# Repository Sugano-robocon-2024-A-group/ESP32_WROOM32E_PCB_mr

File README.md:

# ESP32_WROOM_32E_msd
## 作成・許諾 
Copyright (c) [2024] [益田隆太郎]. All rights reserved.
Sugano Robocon Aチーム (益田隆太郎、大谷卓輝、須崎一眞、藤上晃成)  
### * このソフトウェアパッケージは、3条項BSDライセンスの下、再配布及び使用が許可されます
### @ 2024 Sugano Robocon A team
連絡はX(@Masuda_moto)またはryutaro.masuda@akane.waseda.jpまで
## 外観

## 使用法
production→ESP32_WROOM_32E_msd.zipがガーバーファイルで、JLCPCBに送るとそのままPCBとして出してくれます。
## ピン配置
ESP32はESPマトリックス機能があるため、どのピンを使っても基本的に許されるが、PWMがはけるピンは決まっている。
[こちら](https://docs.sunfounder.com/projects/umsk/ja/latest/07_appendix/esp32_wroom_32e.html)を参照のこと
を参照のこと。
### 足回りピン配置
回路図の通りですが
RFはRightFront、LFはLeftFront、RBはRightBack、LBはLeftBackに対応しています。(例:RF_1とRF_2でモータドライバの正転逆転を制御、RF_PWMで角速度を制御)

GPIO22 RF_1  
GPIO23 RF_2  
GPIO16 RF_PWM  
GPIO18 LF_1  
GPIO19 LF_2  
GPIO21 LF_PWM  
GPIO32 RB_1  
GPIO33 RB_2  
GPIO04 RB_PWM  
GPIO25 LB_1  
GPIO14 LB_2  
GPIO13 LB_PWM  
足回りのモータドライバは[こちら](https://osoyoo.com/2022/02/25/osoyoo-model-y-4-channel-motor-driver/)の市販品を使用しました。

### CAN通信
いろんなサイトで26と27がRXとTXにアサインされていたので使用。うまく動きました。

GPIO26 CAN_RX  
GPIO27 CAN_TX  

### エンコーダピン配置
エンコーダで速度制御のフィードバックをかけたかったのですが、それだとピンが足りません。なのでマイコンを2個使って、CAN通信で情報をおくりあうことにしました。二つのマイコンの基板を共通化させたかったので、ピンを共有させました。
本番では速度のPID制御はあきらめてフィードフォワード制御に変えたので、このピンは使っていません。使いたかったら使うと良いと思います。
この場合、①RFとLFのモータを制御するマイコン②RBとLBのモータを制御するマイコン③上物を制御するマイコンの３つのマイコンでCAN通信をする必要があります。この時、CANバス内のノードが３つなので、終端抵抗を一つの基板だけOFFにする必要があります。SW1はそれ用のスイッチです。
また、ピンが共通になっているので、①のマイコンにおいて

GPIO22 RF_1  
GPIO23 RF_2  
GPIO16 RF_PWM  
GPIO18 LF_1  
GPIO19 LF_2  
GPIO21 LF_PWM  

をモータドライバに接続するときは、エンコーダに接続するピンは

GPIO32 RB_1  
GPIO33 RB_2  
GPIO25 LB_1  
GPIO14 LB_2  

であるという紛らわしさに注意する必要があります。②はその逆で、

GPIO32 RB_1  
GPIO33 RB_2  
GPIO04 RB_PWM  
GPIO25 LB_1  
GPIO14 LB_2  
GPIO13 LB_PWM  

をモータドライバに接続するので、エンコーダに接続するピンは

GPIO22 RF_1  
GPIO23 RF_2  
GPIO18 LF_1  
GPIO19 LF_2  

です。回路図の通りですね。
### 上物
投擲用のモータドライバは秋月で買える[TB67H450](https://akizukidenshi.com/catalog/g/g114753/)を使いました。
投擲のモータは速度フィードバックはかけず、フィードフォワードのみです。

GPIO16 RF_PWM 正転・逆転  
GPIO21 LF_PWM 正転・逆転  
GPIO04 RB_PWM PWM調整  

です。

GPIO13 LB_PWM  
GPIO05 Servo1  

を装填・仰角調整にアサインしました。
上物の電源電圧は2Sのリポバッテリー7.4Vを使用しました。XT30がコネクタです。

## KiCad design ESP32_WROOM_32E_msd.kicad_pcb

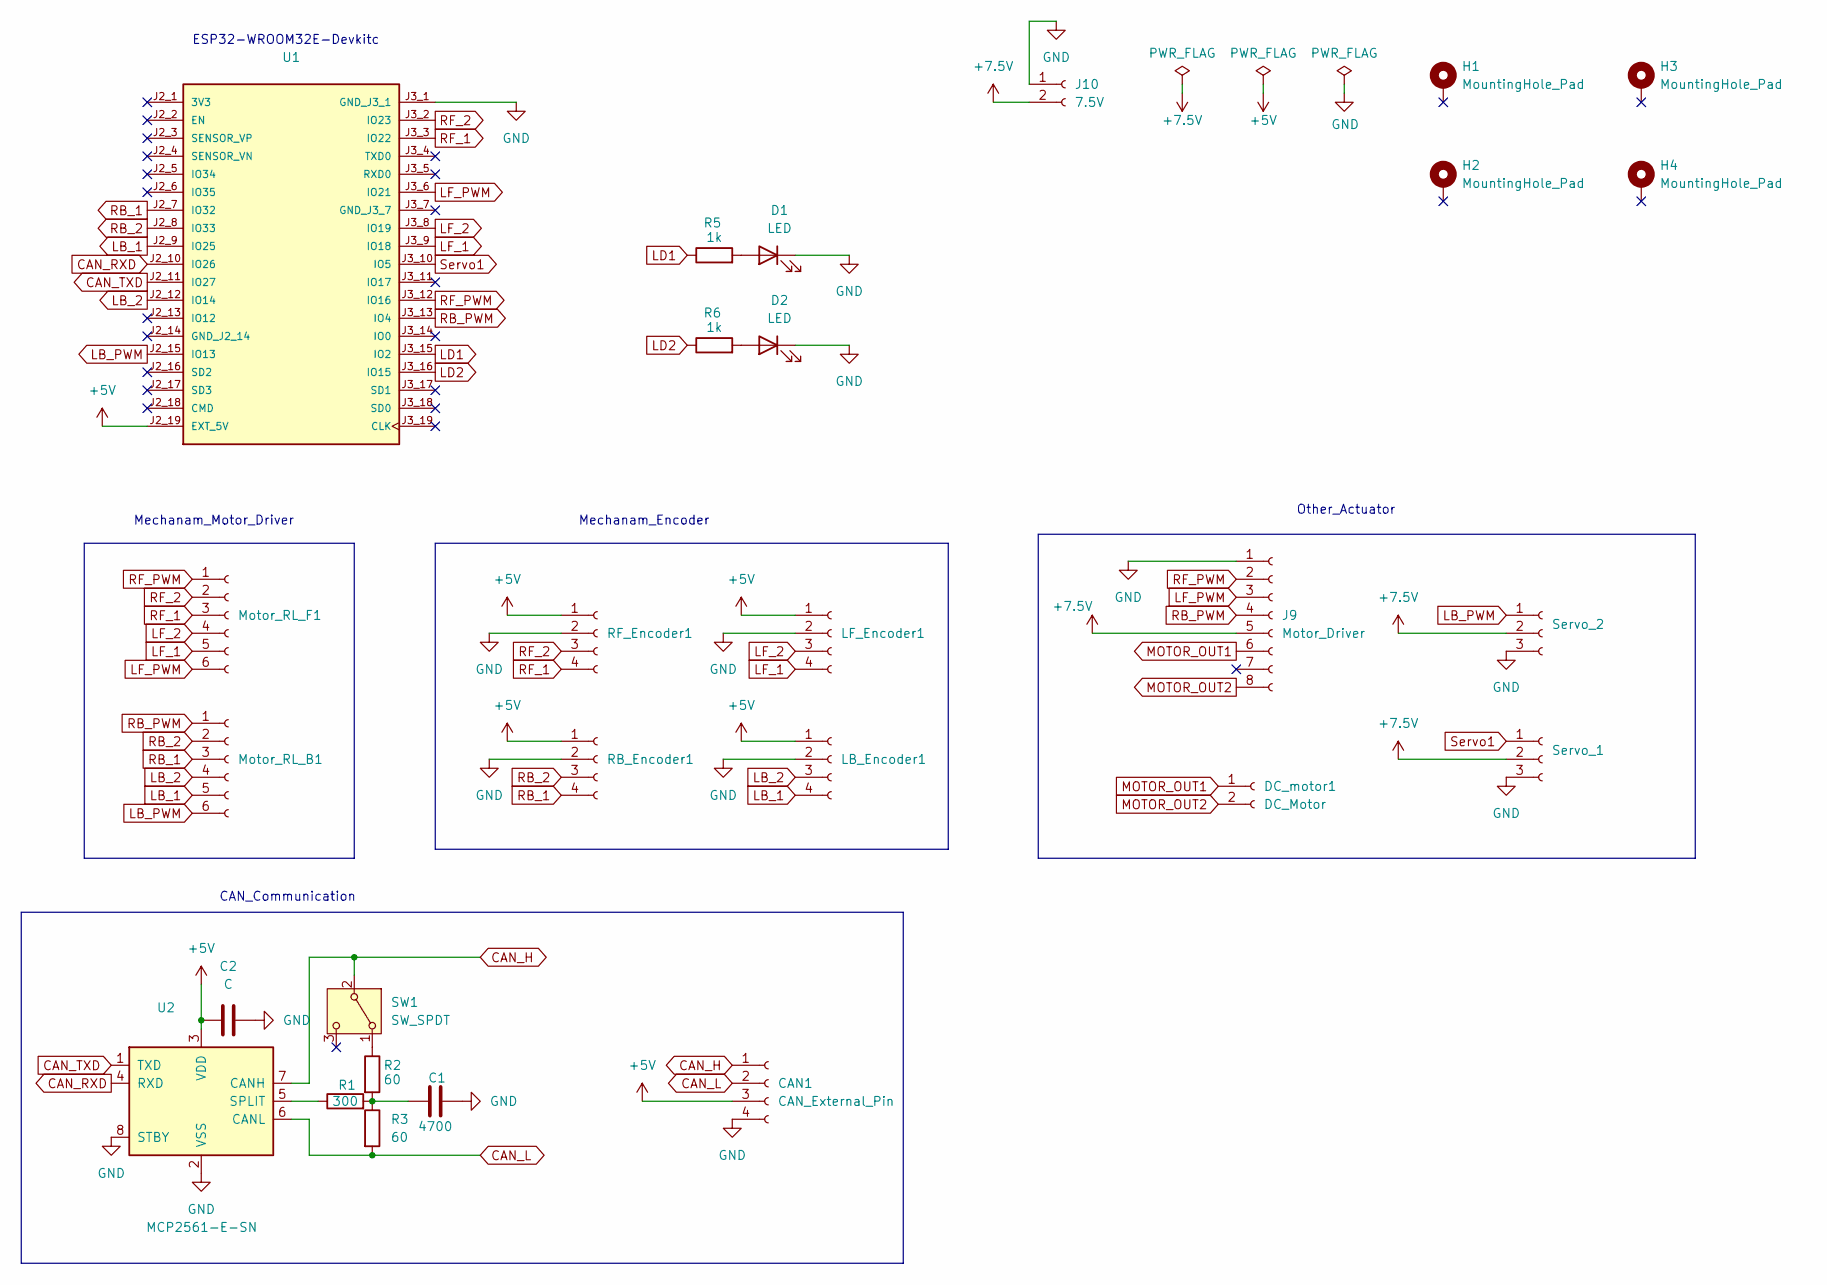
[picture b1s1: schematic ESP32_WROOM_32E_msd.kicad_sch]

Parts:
C1: 4700; C_0603_1608Metric
C2: C; C_0603_1608Metric
CAN1: CAN_External_Pin; JST_XH_B4B-XH-A_1x04_P2.50mm_Vertical
D1, D2: LED; LED_0603_1608Metric
DC_motor1: DC_Motor; JST_XH_B2B-XH-A_1x02_P2.50mm_Vertical
H1, H2, H3, H4: MountingHole_Pad; MountingHole_3.2mm_M3_DIN965_Pad
J9: Motor_Driver; PinHeader_1x08_P2.54mm_Vertical
J10: 7.5V; AMASS_XT30PW-F_1x02_P2.50mm_Horizontal
LB_Encoder1: LB_Encoder; JST_XH_B4B-XH-A_1x04_P2.50mm_Vertical
LF_Encoder1: LF_Encoder; JST_XH_B4B-XH-A_1x04_P2.50mm_Vertical
Motor_RL_B1: Motor_RL_B; JST_XH_B6B-XH-A_1x06_P2.50mm_Vertical
Motor_RL_F1: Motor_RL_F; JST_XH_B6B-XH-A_1x06_P2.50mm_Vertical
R1: 300; R_0603_1608Metric
R2, R3: 60; R_0603_1608Metric
R5, R6: 1k; R_0603_1608Metric
RB_Encoder1: RB_Encoder; JST_XH_B4B-XH-A_1x04_P2.50mm_Vertical
RF_Encoder1: RF_Encoder; JST_XH_B4B-XH-A_1x04_P2.50mm_Vertical
SW1: SW_SPDT; PinHeader_1x03_P2.54mm_Vertical
Servo_1: Servo_1; JST_XH_B3B-XH-A_1x03_P2.50mm_Vertical
Servo_2: Servo_2; JST_XH_B3B-XH-A_1x03_P2.50mm_Vertical
U1: MODULE_ESP32-DEVKITC-32E; PARTREV 1.4
U2: MCP2561-E-SN; SOIC-8_3.9x4.9mm_P1.27mm

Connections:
+5V: C2.1, CAN1.3, LB_Encoder1.1, LF_Encoder1.1, RB_Encoder1.1, RF_Encoder1.1, U1.J2_19 (EXT_5V), U2.3 (VDD)
+7.5V: J9.5, J10.2, Servo_1.2, Servo_2.2
CAN_H: CAN1.1, SW1.2 (B), U2.7 (CANH)
CAN_L: CAN1.2, R3.2, U2.6 (CANL); also elsewhere on the board
CAN_RXD: U1.J2_10 (IO26), U2.4 (RXD)
CAN_TXD: U1.J2_11 (IO27), U2.1 (TXD)
GND: C1.2, C2.2, CAN1.4, D1.1 (K), D2.1 (K), J9.1, J10.1, LB_Encoder1.2, LF_Encoder1.2, RB_Encoder1.2, RF_Encoder1.2, Servo_1.3, Servo_2.3, U1.J3_1 (GND_J3_1), U2.2 (VSS), U2.8 (STBY)
LB_1: LB_Encoder1.4, Motor_RL_B1.5, U1.J2_9 (IO25)
LB_2: LB_Encoder1.3, Motor_RL_B1.4, U1.J2_12 (IO14)
LB_PWM: Motor_RL_B1.6, Servo_2.1, U1.J2_15 (IO13)
LD1: R5.1, U1.J3_15 (IO2)
LD2: R6.1, U1.J3_16 (IO15)
LF_1: LF_Encoder1.4, Motor_RL_F1.5, U1.J3_9 (IO18)
LF_2: LF_Encoder1.3, Motor_RL_F1.4, U1.J3_8 (IO19)
LF_PWM: J9.3, Motor_RL_F1.6, U1.J3_6 (IO21)
MOTOR_OUT1: DC_motor1.1, J9.6
MOTOR_OUT2: DC_motor1.2, J9.8
unnamed: C1.1, R1.2, R2.2, R3.1
unnamed: D1.2 (A), R5.2
unnamed: D2.2 (A), R6.2
unnamed 20: R2.1, SW1.1 (A); also elsewhere on the board
unnamed: R1.1, U2.5 (SPLIT)
RB_1: Motor_RL_B1.3, RB_Encoder1.4, U1.J2_7 (IO32)
RB_2: Motor_RL_B1.2, RB_Encoder1.3, U1.J2_8 (IO33)
RB_PWM: J9.4, Motor_RL_B1.1, U1.J3_13 (IO4)
RF_1: Motor_RL_F1.3, RF_Encoder1.4, U1.J3_3 (IO22)
RF_2: Motor_RL_F1.2, RF_Encoder1.3, U1.J3_2 (IO23)
RF_PWM: J9.2, Motor_RL_F1.1, U1.J3_12 (IO16)
Servo1: Servo_1.1, U1.J3_10 (IO5)

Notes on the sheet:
Mechanam_Motor_Driver
Other_Actuator
ESP32-WROOM32E-Devkitc
CAN_Communication
Mechanam_Encoder

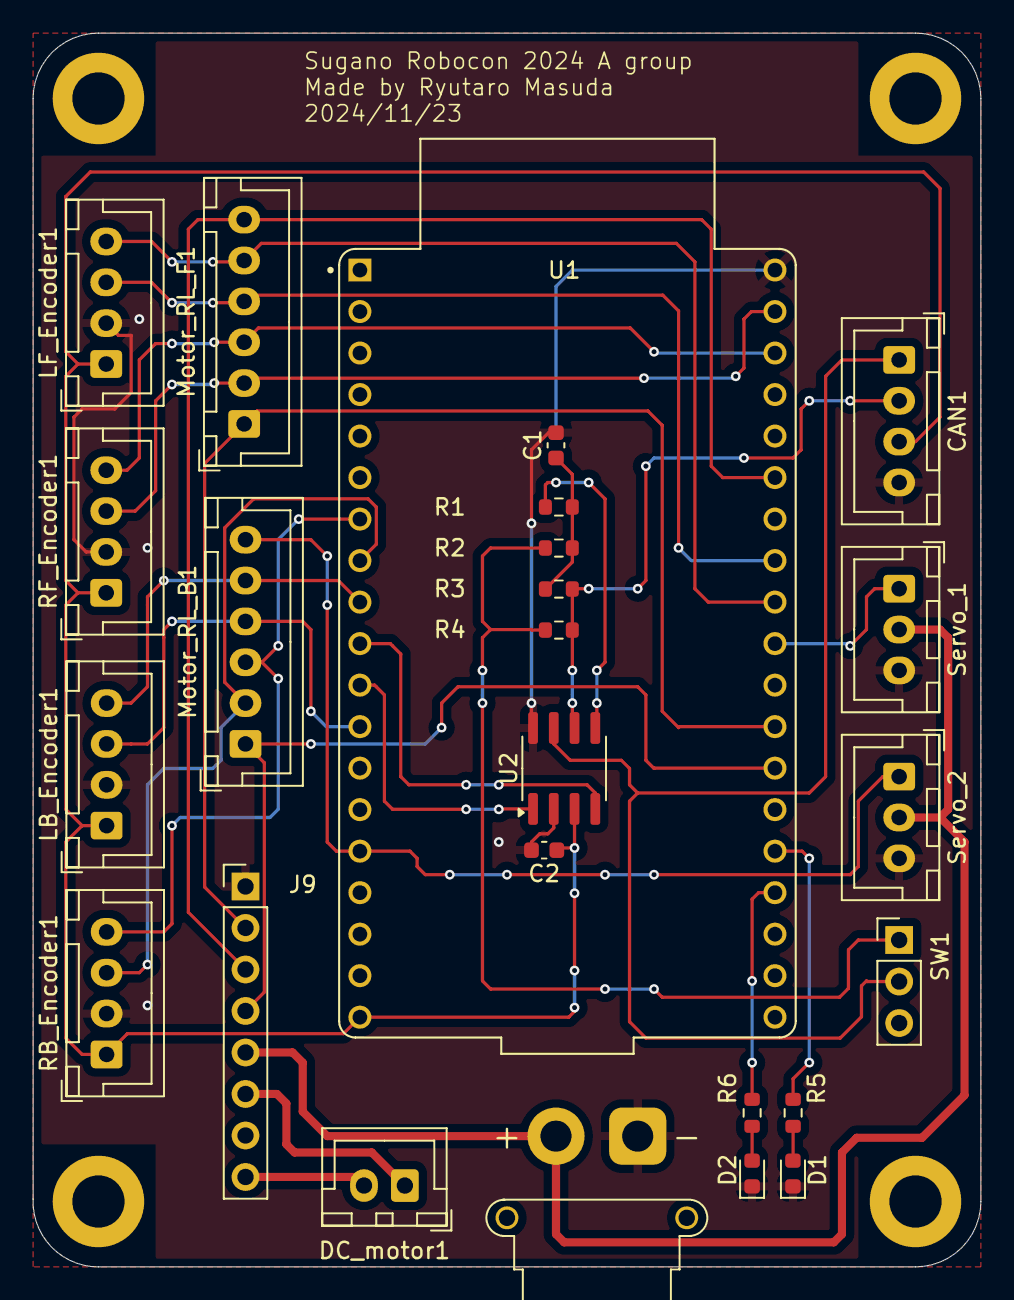
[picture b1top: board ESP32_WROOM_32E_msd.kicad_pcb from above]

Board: 2 copper layers, 58.0 x 75.5 mm, 29 parts (0 on the bottom side), 29 nets.

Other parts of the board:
R4: 120; R_0603_1608Metric

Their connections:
CAN_L: R4.2; also elsewhere on the board
unnamed 20: R4.1; also elsewhere on the board

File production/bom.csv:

Designator,Footprint,Quantity,Value,LCSC Part #
C1,0603,1,4700,
C2,0603,1,C,
CAN1,JST_XH_B4B-XH-A_1x04_P2.50mm_Vertical,1,CAN_External_Pin,
"D1, D2",0603,2,LED,
DC_MOTOR1,JST_XH_B2B-XH-A_1x02_P2.50mm_Vertical,1,DC_Motor,
"H1, H2, H3, H4",MountingHole_3.2mm_M3_DIN965_Pad,4,MountingHole_Pad,
J10,AMASS_XT30PW-F_1x02_P2.50mm_Horizontal,1,7.5V,
J9,PinHeader_1x08_P2.54mm_Vertical,1,Motor_Driver,
LB_ENCODER1,JST_XH_B4B-XH-A_1x04_P2.50mm_Vertical,1,LB_Encoder,
LF_ENCODER1,JST_XH_B4B-XH-A_1x04_P2.50mm_Vertical,1,LF_Encoder,
MOTOR_RL_B1,JST_XH_B6B-XH-A_1x06_P2.50mm_Vertical,1,Motor_RL_B,
MOTOR_RL_F1,JST_XH_B6B-XH-A_1x06_P2.50mm_Vertical,1,Motor_RL_F,
R1,0603,1,300,
"R2, R3",0603,2,60,
R4,0603,1,120,
"R5, R6",0603,2,1k,
RB_ENCODER1,JST_XH_B4B-XH-A_1x04_P2.50mm_Vertical,1,RB_Encoder,
RF_ENCODER1,JST_XH_B4B-XH-A_1x04_P2.50mm_Vertical,1,RF_Encoder,
SERVO_1,JST_XH_B3B-XH-A_1x03_P2.50mm_Vertical,1,Servo_1,
SERVO_2,JST_XH_B3B-XH-A_1x03_P2.50mm_Vertical,1,Servo_2,
SW1,PinHeader_1x03_P2.54mm_Vertical,1,SW_SPDT,
U1,MODULE_ESP32-DEVKITC-32E,1,~,
U2,SOIC-8_3.9x4.9mm_P1.27mm,1,MCP2561-E-SN,

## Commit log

2024-11-15 second commit
2024-11-15 complete pcb
2024-11-19 add mickey
2024-11-22 add encoder pin and motor driver pin
    XH_4×4, pin header_8×1
2024-11-22 add frames
2024-11-24 almost complete
    add Beta Ground,
2024-11-24 complete ver2
2024-11-24 change switch
    because no stock on JLCPCB
2024-11-24 revised wiring thickness
    アクチュエータ部の配線太さを変更
2024-11-29 add step file
2024-12-13 add pictures
